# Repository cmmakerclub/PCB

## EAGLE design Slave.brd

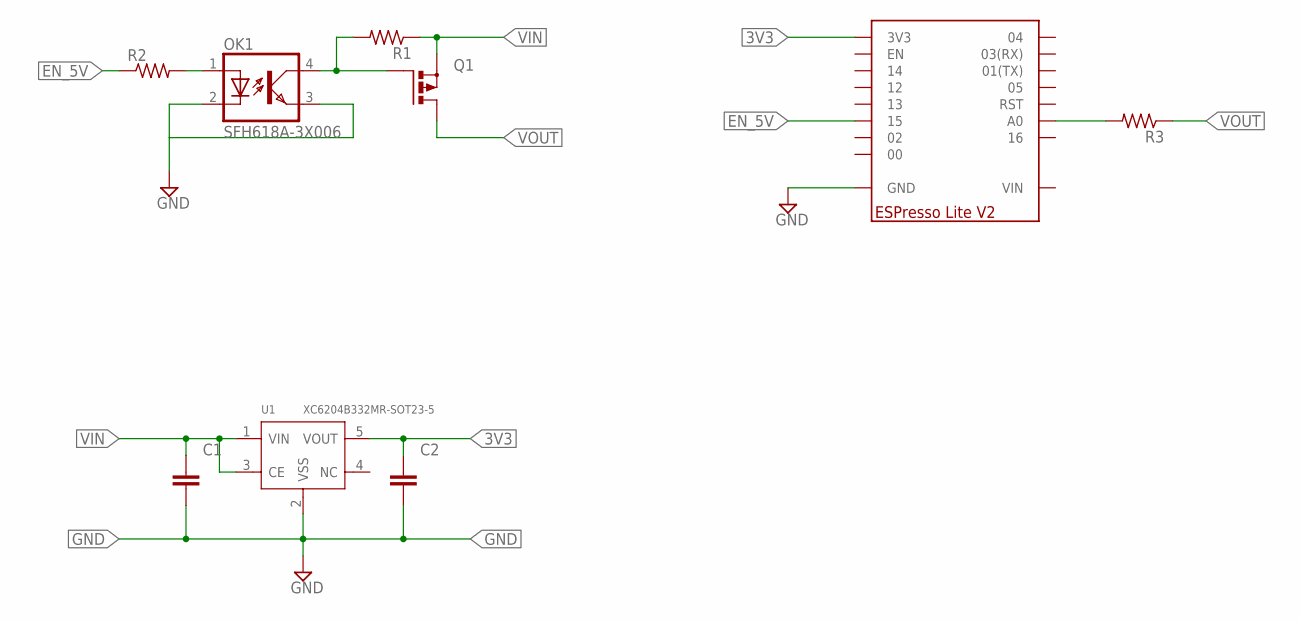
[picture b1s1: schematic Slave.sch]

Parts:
C1, C2: CAPACITOR_NPOL-1206; C1206
OK1: SFH618A-3X006; DIP4-400
Q1: P-MOSFET-SO8; SO-08
R1, R2, R3: R-US_M0805; M0805
U1: XC6204B332MR-SOT23-5; SOT-23-5
U$1: ESPRESSO-LITE-V2

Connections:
3V3: C2.1, U1.5 (VOUT), U$1.3V3
EN_5V: R2.1, U$1.15
GND: C1.2, C2.2, OK1.3 (EMIT), U1.2 (VSS), U$1.GND1 (GND), U$1.GND2 (GND), U$1.GND3 (GND)
unnamed: OK1.1 (A), R2.2
unnamed: OK1.4 (COL), Q1.4 (G), R1.2
unnamed: R3.2, U$1.AO (A0)
VIN: C1.1, Q1.1 (S), Q1.2 (S), Q1.3 (S), R1.1, U1.1 (VIN), U1.3 (CE)
VOUT: Q1.5 (D), Q1.6 (D), Q1.7 (D), Q1.8 (D), R3.1

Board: 2 copper layers, 9 parts (0 on the bottom side), 8 nets, no tracks yet.

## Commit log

2017-06-03 1version
